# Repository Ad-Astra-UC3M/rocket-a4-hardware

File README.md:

View this project on [CADLAB.io](https://cadlab.io/project/30721). 

# Rocket A4 — Hardware

KiCad hardware for the Ad Astra UC3M Rocket A4 project. One folder per board.

| Folder | Contents |
|---|---|
| `flight-computer/` | KiCad project of the flight computer (`.kicad_pro`, `.kicad_sch`, `.kicad_pcb`, project libraries) |
| `ground-station/` | KiCad project of the ground station |
| `docs/` | Datasheets and design decisions |
| `miscellaneous/` | Test boards and experiments not part of the flight design (e.g. `PCB_A4_v2`, first PCB test) |
## Rules
- Each board folder contains a `production/` subfolder (Gerbers, drill files, BOM) **only** when a revision is sent to fabrication. These files are exported from KiCad, never edited by hand.
- KiCad temporary and per-user files are excluded via `.gitignore`.
- Changes go into `main` through a pull request. Review schematic/PCB diffs on CADLAB.
- Workflow guide: see the Ad Astra version control document.

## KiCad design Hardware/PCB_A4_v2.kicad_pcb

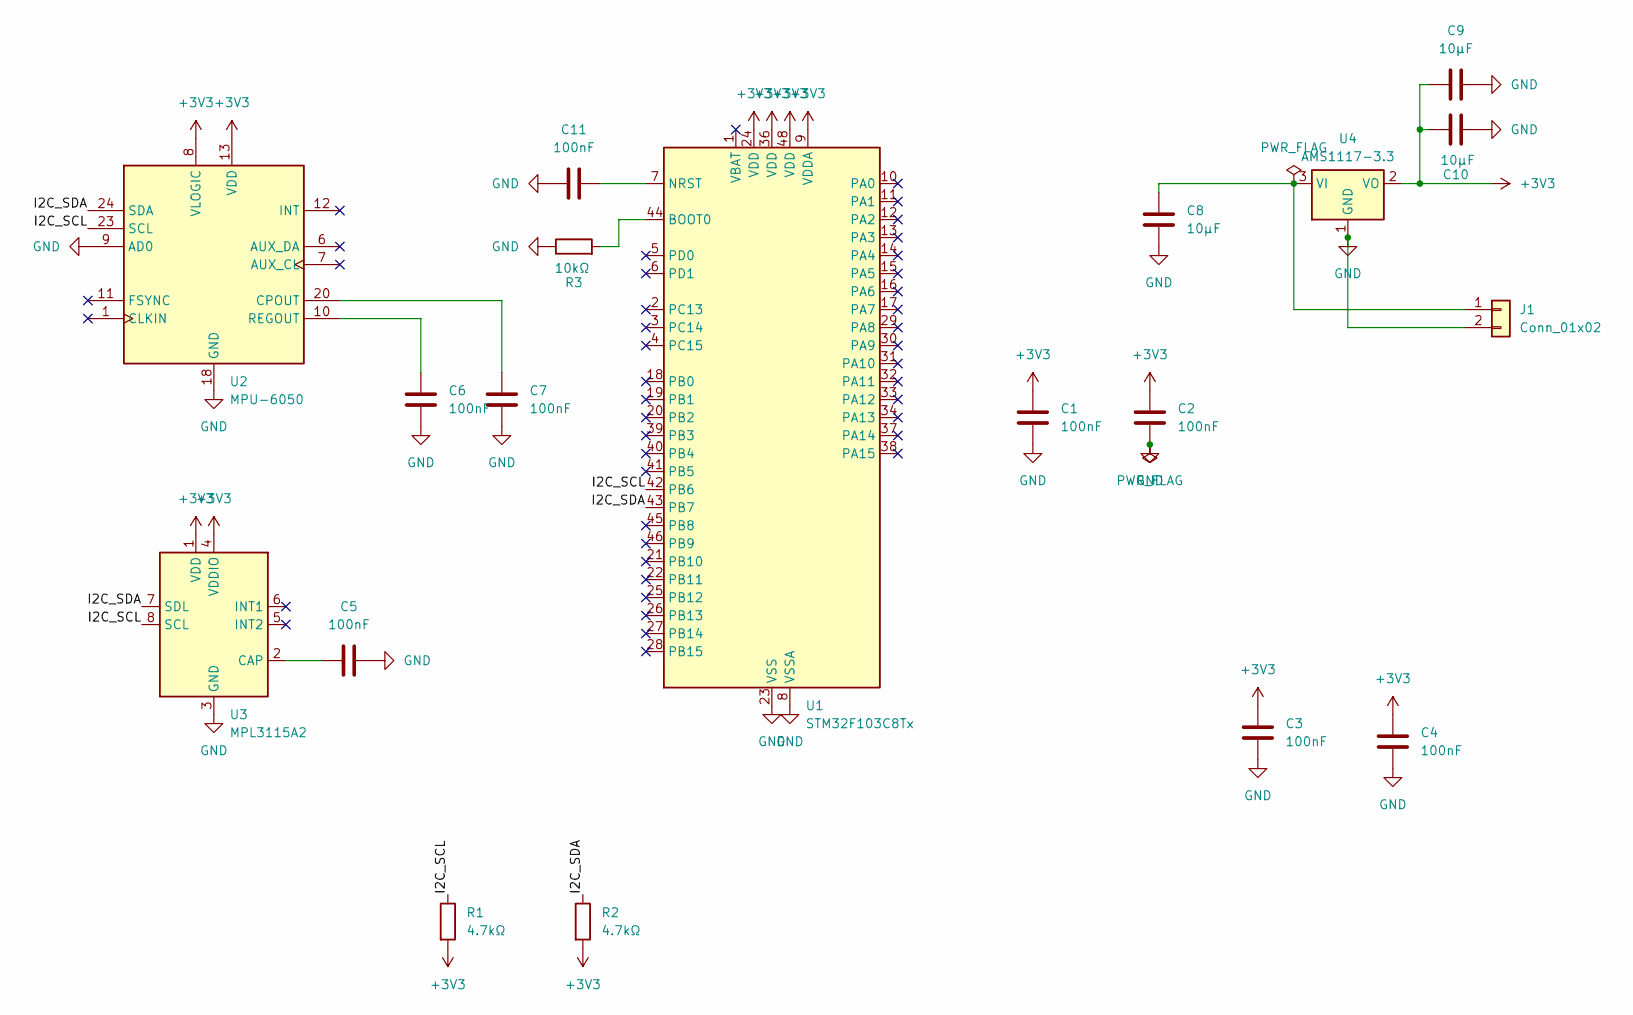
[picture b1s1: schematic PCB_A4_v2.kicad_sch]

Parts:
C1, C2, C3, C4, C5, C6, C7, C11: 100nF; C_0402_1005Metric
C8, C9, C10: 10µF; C_0805_2012Metric
J1: Conn_01x02; JST_PH_B2B-PH-K_1x02_P2.00mm_Vertical
R1, R2: 4.7kΩ; R_0402_1005Metric
R3: 10kΩ; R_0402_1005Metric
U1: STM32F103C8Tx; LQFP-48_7x7mm_P0.5mm
U2: MPU-6050; InvenSense_QFN-24_4x4mm_P0.5mm
U3: MPL3115A2; NXP_LGA-8_3x5mm_P1.25mm_H1.1mm
U4: AMS1117-3.3; SOT-223-3_TabPin2

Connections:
+3V3: C1.1, C2.1, C3.1, C4.1, C9.1, C10.1, R1.2, R2.2, U1.9 (VDDA), U1.24 (VDD), U1.36 (VDD), U1.48 (VDD), U2.8 (VLOGIC), U2.13 (VDD), U3.1 (VDD), U3.4 (VDDIO), U4.2 (VO)
/I2C_SCL: R1.1, U1.42 (PB6), U2.23 (SCL), U3.8 (SCL)
/I2C_SDA: R2.1, U1.43 (PB7), U2.24 (SDA), U3.7 (SDL)
GND: C1.2, C2.2, C3.2, C4.2, C5.2, C6.2, C7.2, C8.2, C9.2, C10.2, C11.1, J1.2, R3.1, U1.8 (VSSA), U1.23 (VSS), U1.35 (VSS), U1.47 (VSS), U2.9 (AD0), U2.18 (GND), U3.3 (GND), U4.1 (GND)
unnamed: C8.1, J1.1, U4.3 (VI)
unnamed: R3.2, U1.44 (BOOT0)
unnamed: C11.2, U1.7 (NRST)
unnamed: C7.1, U2.20 (CPOUT)
unnamed: C6.1, U2.10 (REGOUT)
unnamed: C5.1, U3.2 (CAP)

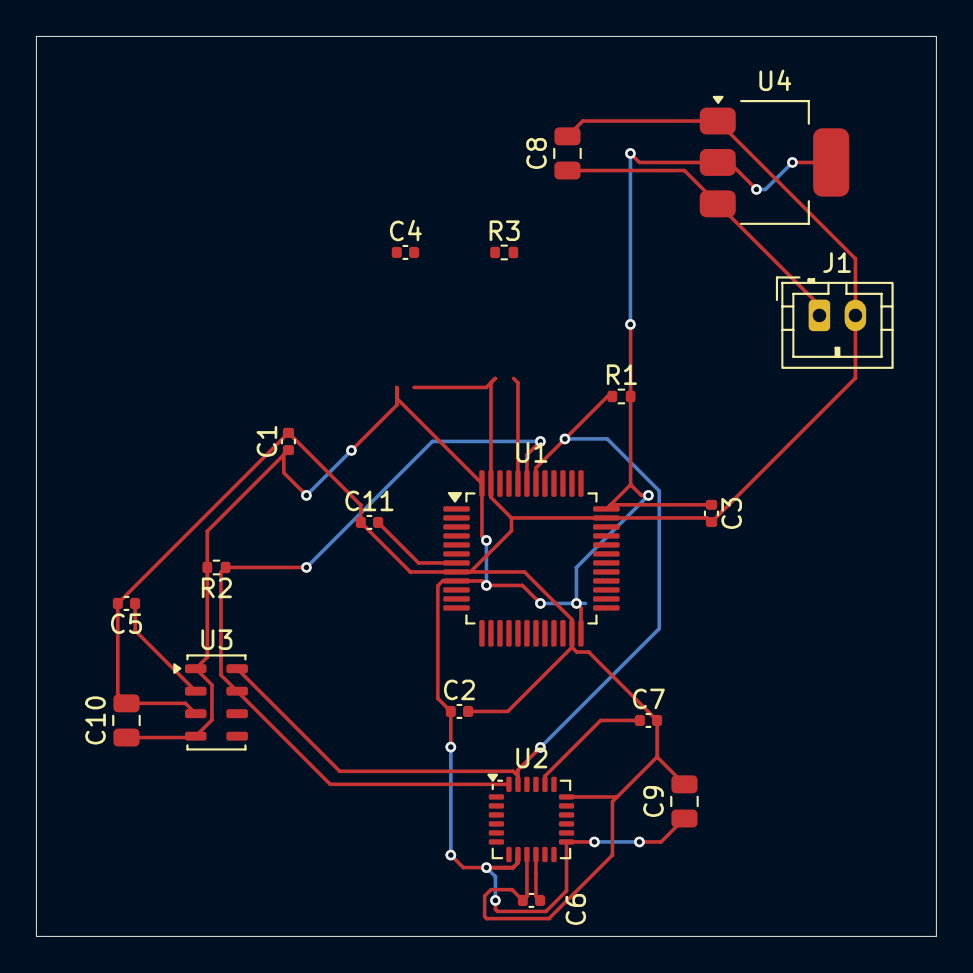
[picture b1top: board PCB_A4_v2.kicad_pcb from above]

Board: 2 copper layers, 50.0 x 50.0 mm, 19 parts (0 on the bottom side), 10 nets.

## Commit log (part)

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2026-06-22 Fix typo in README regarding hardware
2026-06-22 chore: init repository structure
2026-06-22 Revise README to include detailed repository structure
    Expanded the README to provide detailed information about the repository structure and its contents, including sections for Hardware, Docs, Production, Simulation, and CAD.
2026-06-22 Refine descriptions in README.md
    Updated README.md to improve clarity and consistency in descriptions.
2026-06-22 Backlink to CADLAB.io has been added.
2026-06-22 Revise .gitignore for KiCad project files
    Updated .gitignore to include additional temporary and backup file patterns, and removed obsolete entries.
2026-06-22 First pcb test
2026-06-26 Move capacitor and resistance
